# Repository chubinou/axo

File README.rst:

AXO
###

A simple eurorack logic module

* `axo` full schematics
* `axo_back` main board
* `axo_middle` connector board
* `axo_front` face plate

LICENSE
#######

This work by Pierre Lamot is licensed under CC BY-NC 4.0. To view a copy of this license, visit https://creativecommons.org/licenses/by-nc/4.0/

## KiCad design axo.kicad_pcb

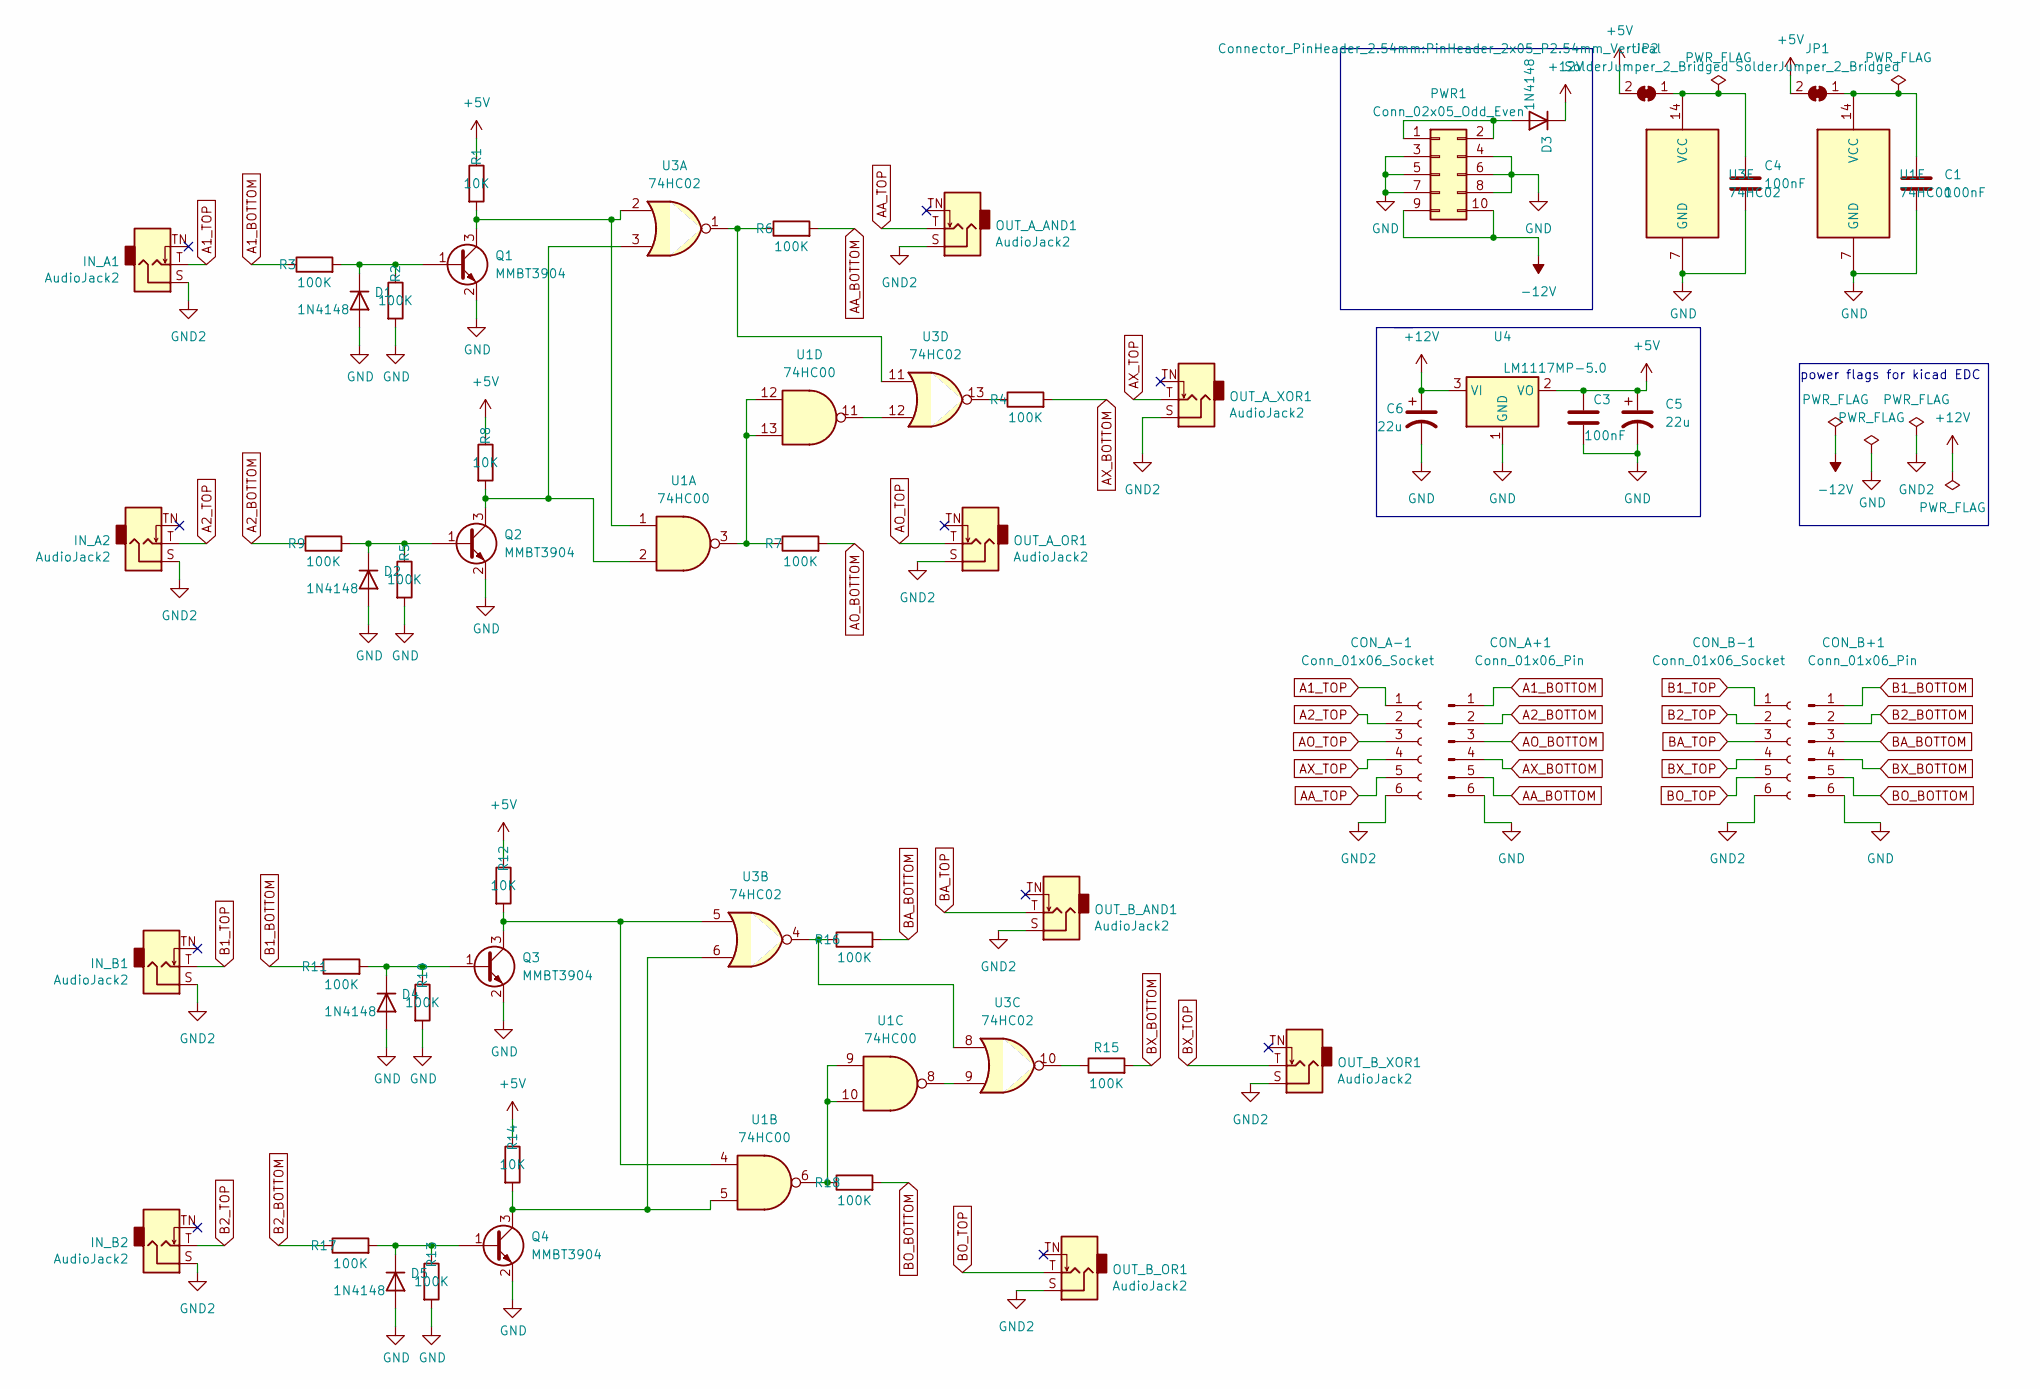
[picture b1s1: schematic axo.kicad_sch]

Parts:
C1, C3, C4: 100nF; C_0805_2012Metric; LCSC C49678
C5, C6: 22u; CP_Elec_6.3x5.4; LCSC C3001215
CON_A+1: Conn_01x06_Pin; PinHeader_1x06_P2.54mm_Vertical
CON_A-1: Conn_01x06_Socket; PinSocket_1x06_P2.54mm_Vertical
CON_B+1: Conn_01x06_Pin; PinHeader_1x06_P2.54mm_Vertical
CON_B-1: Conn_01x06_Socket; PinSocket_1x06_P2.54mm_Vertical
D1, D2, D3, D4, D5: 1N4148; D_SOD-323; LCSC C2128
IN_A1, IN_A2: AudioJack2; Jack_3.5mm_QingPu_WQP-PJ398SM_Vertical
IN_B1, IN_B2: AudioJack2; Jack_3.5mm_QingPu_WQP-PJ398SM_Vertical
JP1, JP2: SolderJumper_2_Bridged; SolderJumper-2_P1.3mm_Bridged_Pad1.0x1.5mm
OUT_A_AND1: AudioJack2; Jack_3.5mm_QingPu_WQP-PJ398SM_Vertical
OUT_A_OR1: AudioJack2; Jack_3.5mm_QingPu_WQP-PJ398SM_Vertical
OUT_A_XOR1: AudioJack2; Jack_3.5mm_QingPu_WQP-PJ398SM_Vertical
OUT_B_AND1: AudioJack2; Jack_3.5mm_QingPu_WQP-PJ398SM_Vertical
OUT_B_OR1: AudioJack2; Jack_3.5mm_QingPu_WQP-PJ398SM_Vertical
OUT_B_XOR1: AudioJack2; Jack_3.5mm_QingPu_WQP-PJ398SM_Vertical
PWR1: Conn_02x05_Odd_Even; PinHeader_2x05_P2.54mm_Vertical
Q1, Q2, Q3, Q4: MMBT3904; SOT-23; LCSC C20526
R1, R8, R12, R14: 10K; R_0603_1608Metric; LCSC C25804
R2, R3, R4, R5, R6, R7, R9, R10, R11, R13, R15, R16, R17, R18: 100K; R_0603_1608Metric; LCSC C25803
U1: 74HC00; SOIC-14_3.9x8.7mm_P1.27mm; LCSC C155451
U3: 74HC02; SOIC-14_3.9x8.7mm_P1.27mm; LCSC C5588
U4: LM1117MP-5.0; SOT-223; LCSC C6187

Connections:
+5V: C3.1, C5.1, JP1.2 (B), JP2.2 (B), R1.1, R8.1, R12.1, R14.1, U4.2 (VO)
+12V: C6.1, D3.1 (K), U4.3 (VI)
-12V: PWR1.9, PWR1.10
A1_BOTTOM: CON_A+1.1, R3.1
A1_TOP: CON_A-1.1, IN_A1.T
A2_BOTTOM: CON_A+1.2, R9.1
A2_TOP: CON_A-1.2, IN_A2.T
AA_BOTTOM: CON_A+1.5, R6.2
AA_TOP: CON_A-1.5, OUT_A_AND1.T
AO_BOTTOM: CON_A+1.3, R7.2
AO_TOP: CON_A-1.3, OUT_A_OR1.T
AX_BOTTOM: CON_A+1.4, R4.2
AX_TOP: CON_A-1.4, OUT_A_XOR1.T
B1_BOTTOM: CON_B+1.1, R11.1
B1_TOP: CON_B-1.1, IN_B1.T
B2_BOTTOM: CON_B+1.2, R17.1
B2_TOP: CON_B-1.2, IN_B2.T
BA_BOTTOM: CON_B+1.3, R16.2
BA_TOP: CON_B-1.3, OUT_B_AND1.T
BO_BOTTOM: CON_B+1.5, R18.2
BO_TOP: CON_B-1.5, OUT_B_OR1.T
BX_BOTTOM: CON_B+1.4, R15.2
BX_TOP: CON_B-1.4, OUT_B_XOR1.T
GND: C1.2, C3.2, C4.2, C5.2, C6.2, CON_A+1.6, CON_B+1.6, D1.2 (A), D2.2 (A), D4.2 (A), D5.2 (A), PWR1.3, PWR1.4, PWR1.5, PWR1.6, PWR1.7, PWR1.8, Q1.2 (E), Q2.2 (E), Q3.2 (E), Q4.2 (E), R2.2, R5.2, R10.2, R13.2, U1.7 (GND), U3.7 (GND), U4.1 (GND)
GND2: CON_A-1.6, CON_B-1.6, IN_A1.S, IN_A2.S, IN_B1.S, IN_B2.S, OUT_A_AND1.S, OUT_A_OR1.S, OUT_A_XOR1.S, OUT_B_AND1.S, OUT_B_OR1.S, OUT_B_XOR1.S
unnamed: D1.1 (K), Q1.1 (B), R2.1, R3.2
unnamed: D2.1 (K), Q2.1 (B), R5.1, R9.2
unnamed: D3.2 (A), PWR1.1, PWR1.2
unnamed: D4.1 (K), Q3.1 (B), R10.1, R11.2
unnamed: D5.1 (K), Q4.1 (B), R13.1, R17.2
unnamed: C1.1, JP1.1 (A), U1.14 (VCC)
unnamed: C4.1, JP2.1 (A), U3.14 (VCC)
unnamed: Q1.3 (C), R1.2, U1.1, U3.2
unnamed: Q2.3 (C), R8.2, U1.2, U3.3
unnamed: Q3.3 (C), R12.2, U1.4, U3.5
unnamed: Q4.3 (C), R14.2, U1.5, U3.6
unnamed: R4.1, U3.13
unnamed: R6.1, U3.1, U3.11
unnamed: R7.1, U1.3, U1.12, U1.13
unnamed: R15.1, U3.10
unnamed: R16.1, U3.4, U3.8
unnamed: R18.1, U1.6, U1.9, U1.10
unnamed: U1.8, U3.9
unnamed: U1.11, U3.12

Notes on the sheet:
power flags for kicad EDC

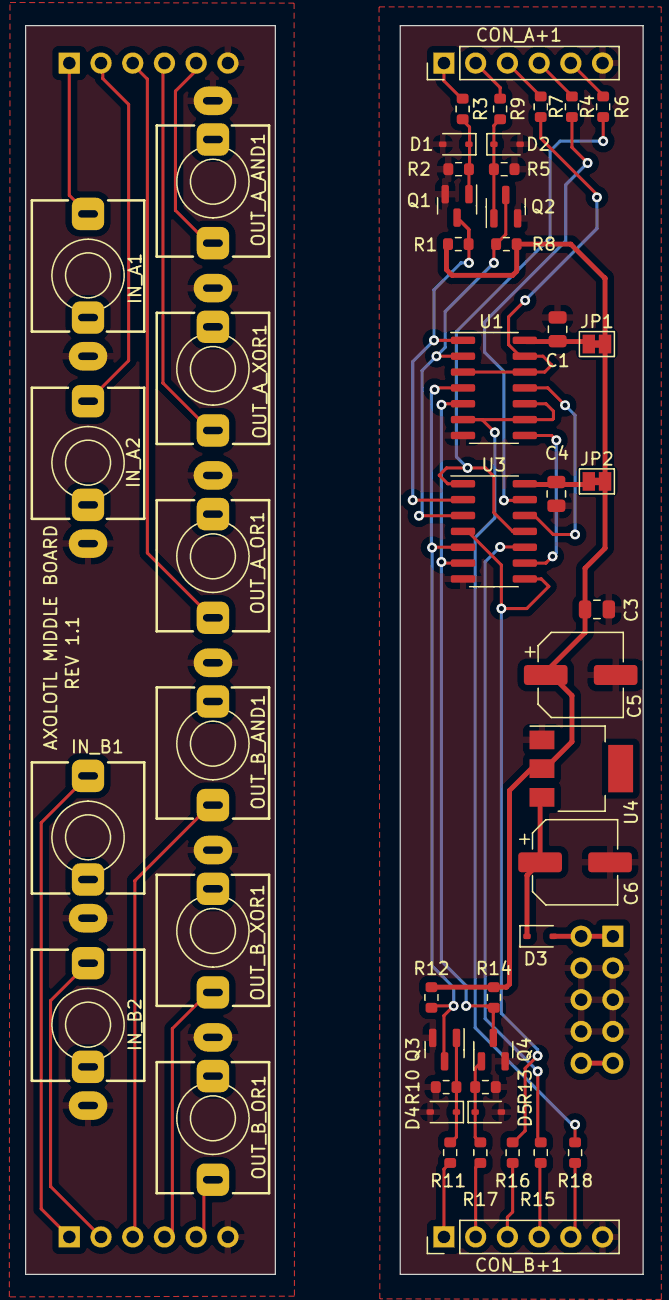
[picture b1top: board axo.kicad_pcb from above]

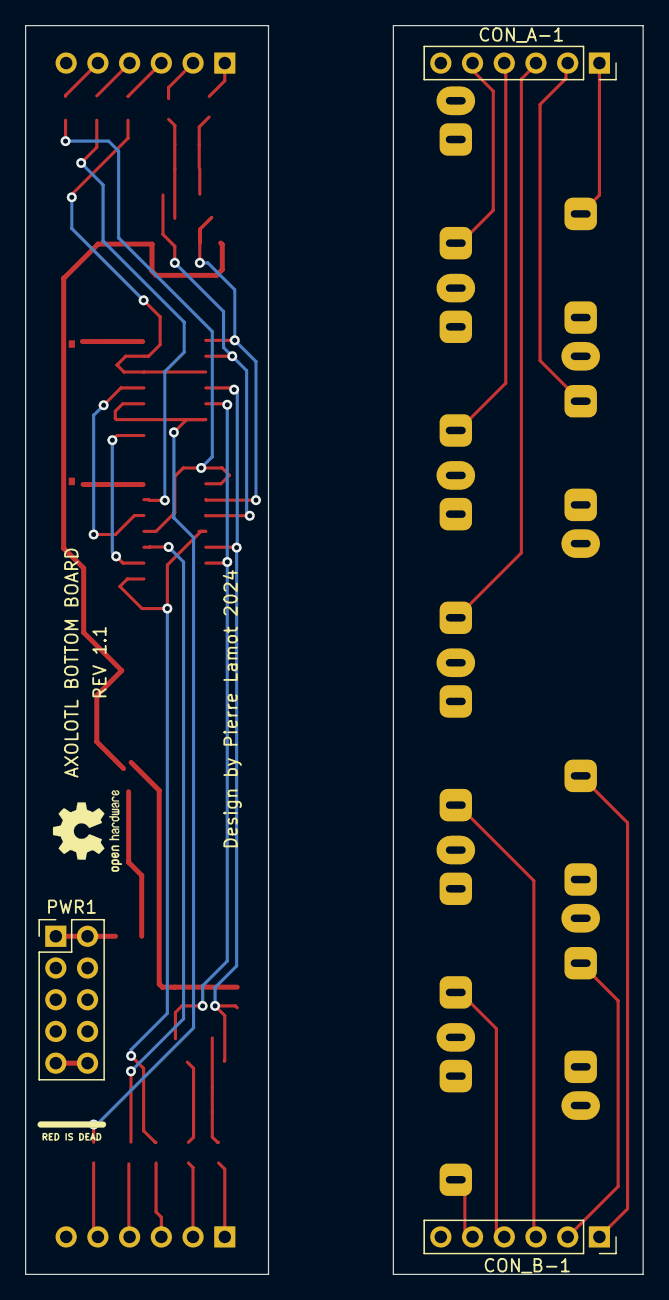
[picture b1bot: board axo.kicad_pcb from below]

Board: 2 copper layers, 49.4 x 100.0 mm, 52 parts (3 on the bottom side), 44 nets.

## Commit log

2024-01-28 axo: init
2024-02-01 replace xor by nand/nor logic
2024-02-09 update artwork
2024-02-10 update pcb
2024-02-10 add svg layer splitter for import
2025-01-01 add readme
2025-01-01 add license
2025-01-01 Create LICENSE
